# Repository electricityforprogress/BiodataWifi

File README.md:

# BiodataWifi
Biodata Sonification system using ESP8266 and Adafruit CircuitPlayground Classic

Biodata Sonification is a process to translate complex real-time sensor data into musical notes and controls, exploring the auditory sensory modality to provide insights into invisible phenomenon. 

Included in this repository are an Arduino Sketch for the Adafruit Circuit Playground 32u4 'Classic' and a Server in Processing3.  Multiple Biodata Nodes can be configured on a Wifi network and their data aggregated by the Server.  Sending MIDI data to software like Ableton Live, dynamic synthesized sounds can be created.

Using the Circuit Playground Switch, Serial data can be output (+) or USB MIDI connectivity (-)
Serial data is represented using the Serial Plotter :
  * Change - Light Blue
  * Threshold - Grey
  * Delta - Magenta
  * Minium - Orange
  * Maximum - Green
  * Standard Deviation - Red
  * Average - Blue

3D Printed Enclosure - 
https://www.tinkercad.com/embed/lpzT7Wl8fgM?editbtn=1

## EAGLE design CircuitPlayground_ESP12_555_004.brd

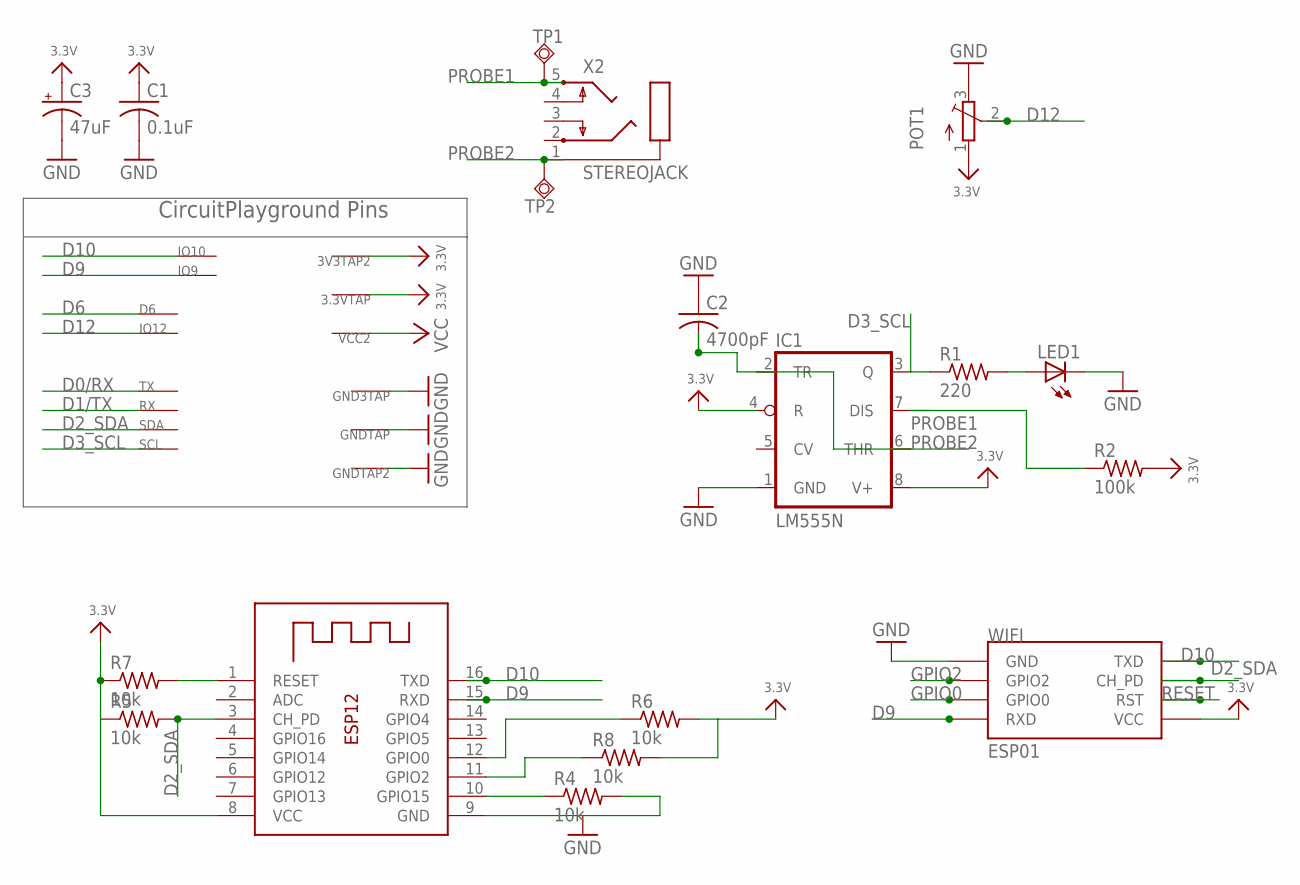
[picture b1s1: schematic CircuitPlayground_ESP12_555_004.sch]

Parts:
3.3VTAP, 3V3TAP2: SEWTAP-ALLIGATOR; SEWALLI
C1: 0.1uF; C025-030X050
C2: 4700pF; C025-030X050
C3: 47uF; E2-4
D6: SEWTAP-ALLIGATOR; SEWALLI
GND3TAP: SEWTAP-ALLIGATOR; SEWALLI
GNDTAP, GNDTAP2: SEWTAP-ALLIGATOR; SEWALLI
IC1: LM555N; DIL08-ROUND
IO9, IO10, IO12: SEWTAP-ALLIGATOR; SEWALLI
LED1: LED5MM
POT1: TRIMPOT3386; TRIM-3386
R1: 220; R1206
R2: 100k; R1206
R4, R5, R6, R7, R8: 10k; R1206
RX: SEWTAP-ALLIGATOR; SEWALLI
SCL: SEWTAP-ALLIGATOR; SEWALLI
SDA: SEWTAP-ALLIGATOR; SEWALLI
TP1, TP2: TPSQTP20R; TP20R
TX: SEWTAP-ALLIGATOR; SEWALLI
VCC2: SEWTAP-ALLIGATOR; SEWALLI
WIFI: ESP01
X1: ESP-12
X2: STEREOJACK; STX3100

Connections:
3.3V: 3.3VTAP.P$1, 3V3TAP2.P$1, C1.1, C3.+, IC1.4 (R), IC1.8 (V+), POT1.1 (A), R2.2, R5.1, R6.2, R7.1, R8.2, WIFI.VCC, X1.8 (VCC)
D0/RX: TX.P$1
D1/TX: RX.P$1
D2_SDA: R5.2, SDA.P$1, WIFI.CH_PD, X1.3 (CH_PD)
D3_SCL: IC1.3 (Q), R1.1, SCL.P$1
D6: D6.P$1
D9: IO9.P$1, WIFI.RX (RXD), X1.15 (RXD)
D10: IO10.P$1, WIFI.TX (TXD), X1.16 (TXD)
D12: IO12.P$1, POT1.2 (S)
GND: C1.2, C2.1, C3.-, GND3TAP.P$1, GNDTAP.P$1, GNDTAP2.P$1, IC1.1 (GND), LED1.K (C), POT1.3 (E), R4.2, WIFI.GND, X1.9 (GND)
GPIO0: R6.1, WIFI.GPIO0, X1.12 (GPIO0)
GPIO2: R8.1, WIFI.GPIO2, X1.11 (GPIO2)
unnamed: R4.1, X1.10 (GPIO15)
unnamed: LED1.A, R1.2
PROBE1: IC1.7 (DIS), R2.1, TP1.TP, X2.5
PROBE2: C2.2, IC1.2 (TR), IC1.6 (THR), TP2.TP, X2.1
RESET: R7.2, WIFI.RST, X1.1 (RESET)
VCC: VCC2.P$1

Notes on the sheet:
CircuitPlayground Pins

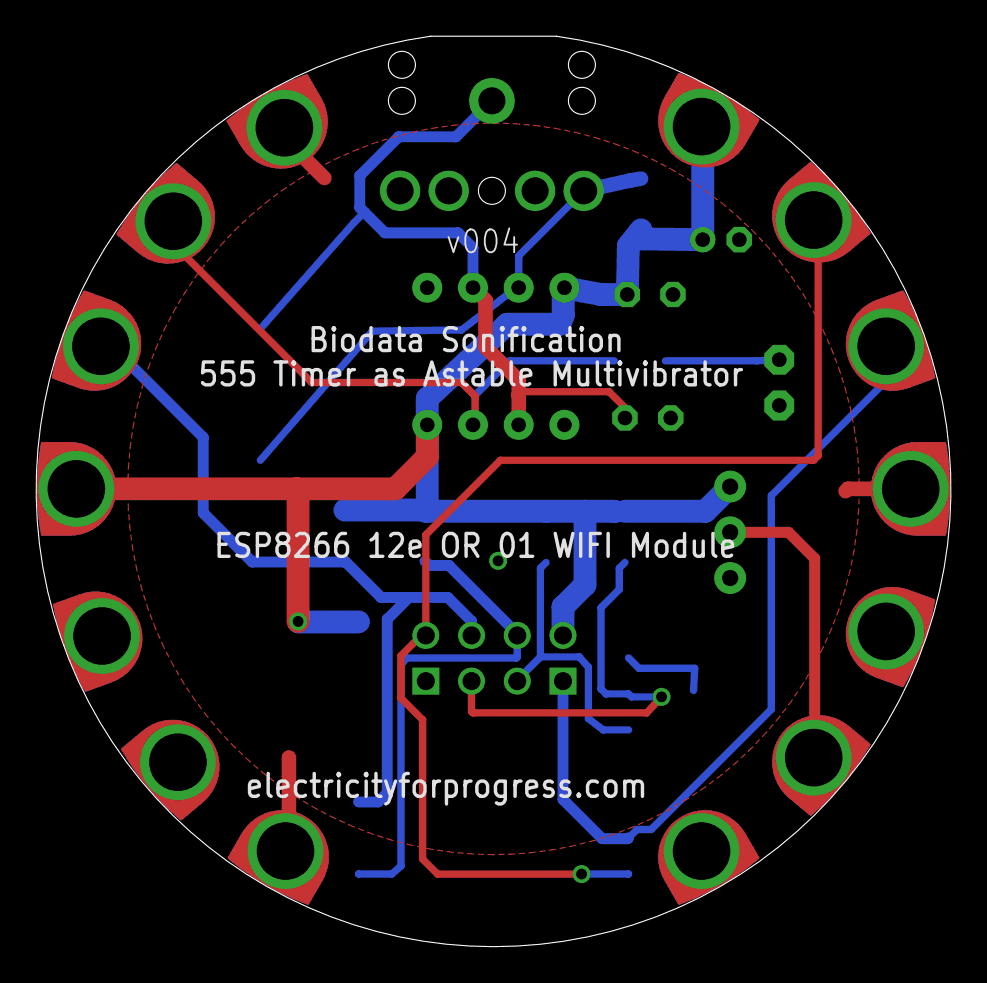
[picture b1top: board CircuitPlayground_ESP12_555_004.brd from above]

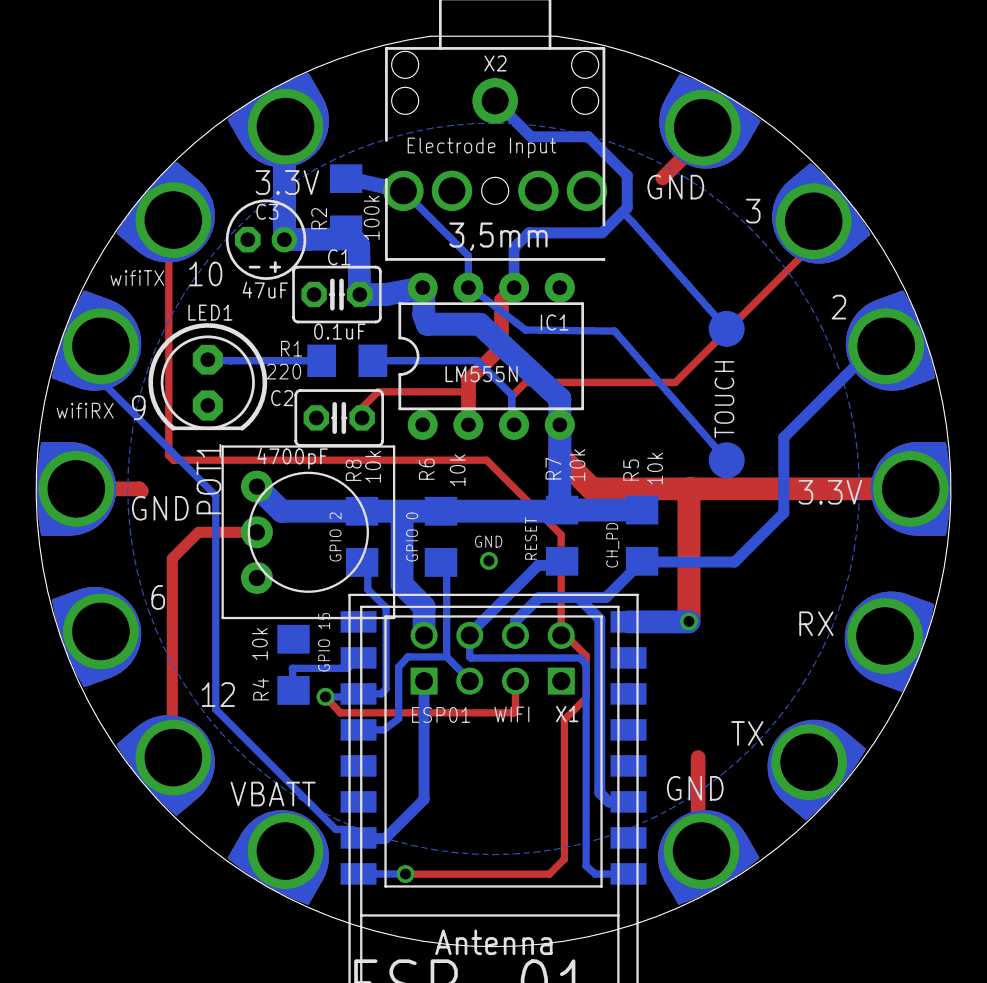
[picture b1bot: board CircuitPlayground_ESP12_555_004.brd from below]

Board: 2 copper layers, 50.8 x 50.6 mm, 32 parts (18 on the bottom side), 14 nets.

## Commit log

2017-09-18 Board designs

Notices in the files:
parts and their libraries:
microbuilder: This work is placed in the public domain, and may be freely used for commercial and non-commercial work with the following conditions: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
